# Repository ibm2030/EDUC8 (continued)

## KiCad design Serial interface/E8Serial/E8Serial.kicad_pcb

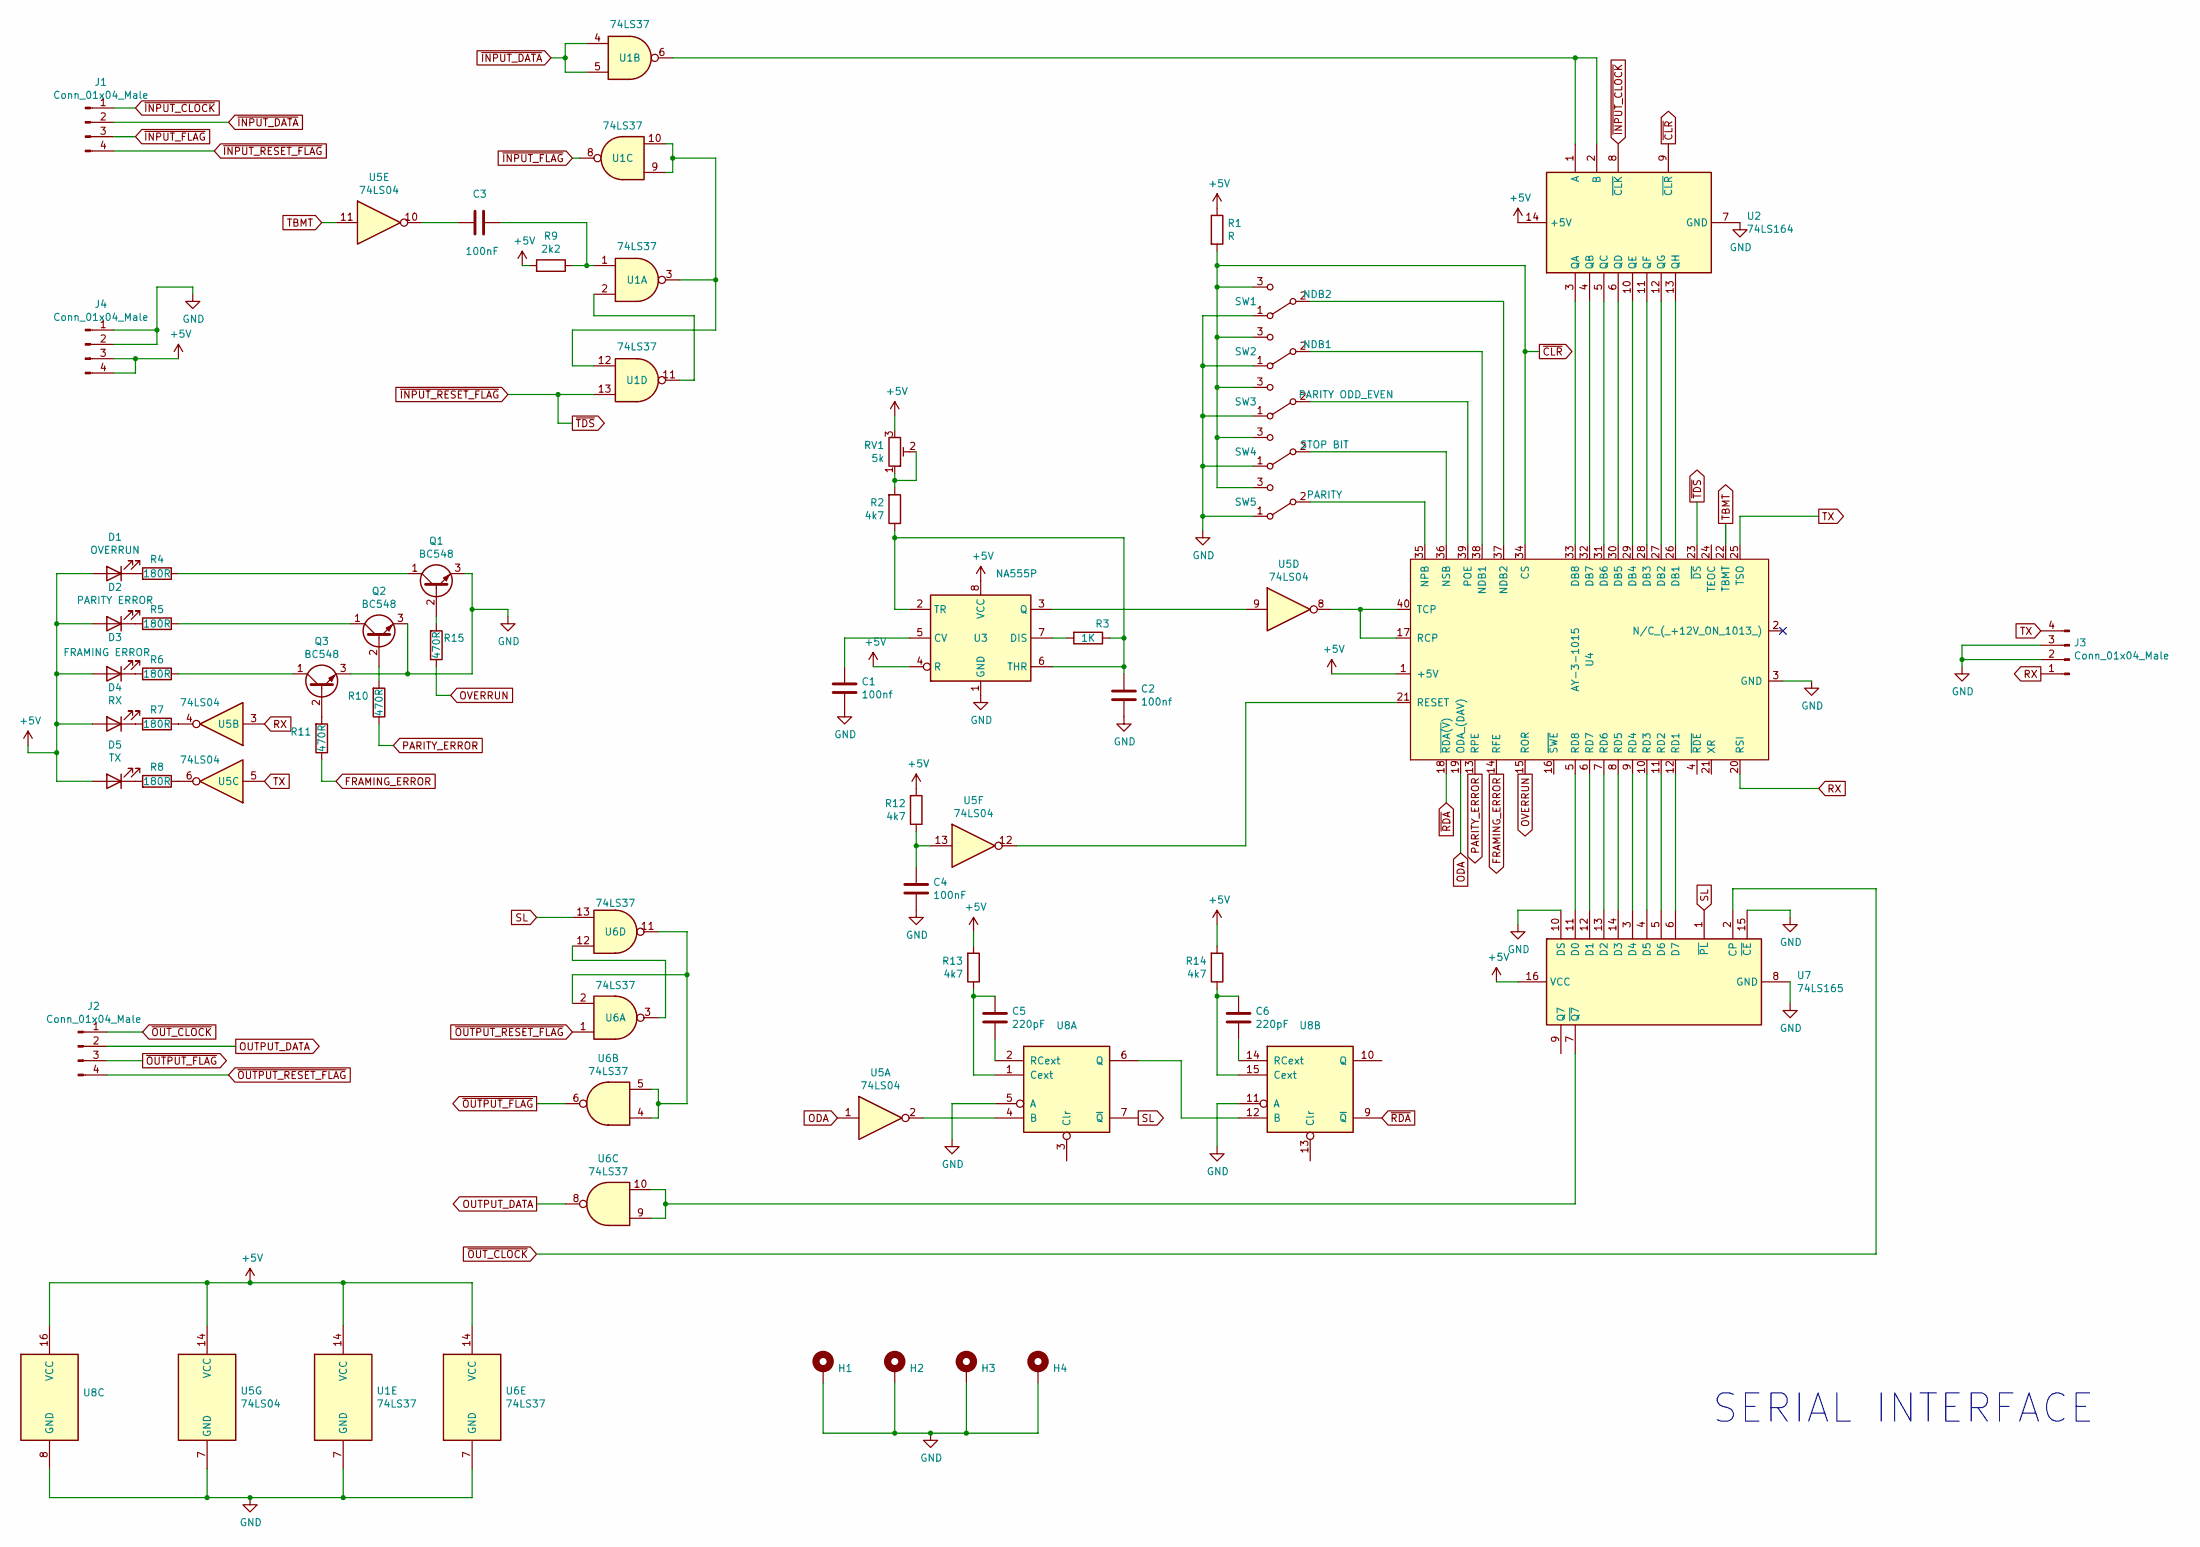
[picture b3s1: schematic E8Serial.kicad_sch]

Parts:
C1, C2: 100nf; C_Disc_D10.0mm_W2.5mm_P5.00mm
C3, C4: 100nF; C_Disc_D10.0mm_W2.5mm_P5.00mm
C5, C6: 220pF; C_Disc_D8.0mm_W2.5mm_P5.00mm
D1: OVERRUN; LED_D5.0mm_Horizontal_O3.81mm_Z9.0mm
D2: PARITY ERROR; LED_D5.0mm_Horizontal_O3.81mm_Z9.0mm
D3: FRAMING ERROR; LED_D5.0mm_Horizontal_O3.81mm_Z9.0mm
D4: RX; LED_D5.0mm_Horizontal_O3.81mm_Z9.0mm
D5: TX; LED_D5.0mm_Horizontal_O3.81mm_Z9.0mm
H1, H2, H3, H4: MountingHole_Pad; MountingHole_3.2mm_M3_Pad_Via
J1, J2, J3, J4: Conn_01x04_Male; PinHeader_1x04_P2.54mm_Vertical
Q1, Q2, Q3: BC548; TO-92_Inline_Wide
R1: R; R_Axial_DIN0207_L6.3mm_D2.5mm_P10.16mm_Horizontal
R2, R12, R13, R14: 4k7; R_Axial_DIN0207_L6.3mm_D2.5mm_P10.16mm_Horizontal
R3: 1K; R_Axial_DIN0207_L6.3mm_D2.5mm_P10.16mm_Horizontal
R4, R5, R6, R7, R8: 180R; R_Axial_DIN0207_L6.3mm_D2.5mm_P10.16mm_Horizontal
R9: 2k2; R_Axial_DIN0207_L6.3mm_D2.5mm_P10.16mm_Horizontal
R10, R11, R15: 470R; R_Axial_DIN0207_L6.3mm_D2.5mm_P10.16mm_Horizontal
RV1: 5k; Potentiometer_Bourns_3006P_Horizontal
SW1: NDB2; S1320_SPDP_Toggle_switch_PCB_right_angle
SW2: NDB1; S1320_SPDP_Toggle_switch_PCB_right_angle
SW3: PARITY ODD_EVEN; S1320_SPDP_Toggle_switch_PCB_right_angle
SW4: STOP BIT; S1320_SPDP_Toggle_switch_PCB_right_angle
SW5: PARITY; S1320_SPDP_Toggle_switch_PCB_right_angle
U1, U6: 74LS37; DIP-14_W7.62mm
U2: 74LS164; DIP-14_W7.62mm
U3: NA555P; DIP-8_W7.62mm
U4: AY-3-1015; DIP-40_W15.24mm
U5: 74LS04; DIP-14_W7.62mm
U7: 74LS165; DIP-16_W7.62mm
U8: DIP-16_W7.62mm_Socket_LongPads

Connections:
+5V: D1.2 (A), D2.2 (A), D3.2 (A), D4.2 (A), D5.2 (A), J4.3, J4.4, R1.1, R9.2, R12.2, R13.2, R14.2, RV1.3, U1.14 (VCC), U2.14 (+5V), U3.4 (R), U3.8 (VCC), U4.1 (+5V), U5.14 (VCC), U6.14 (VCC), U7.16 (VCC), U8.16 (VCC)
FRAMING_ERROR: R11.1, U4.14 (RFE)
GND: C1.2, C2.2, C4.2, H1.1, H2.1, H3.1, H4.1, J3.2, J3.3, J4.1, J4.2, Q1.3 (E), Q2.3 (E), Q3.3 (E), SW1.1 (A), SW2.1 (A), SW3.1 (A), SW4.1 (A), SW5.1 (A), U1.7 (GND), U2.7 (GND), U3.1 (GND), U4.3 (GND), U5.7 (GND), U6.7 (GND), U7.8 (GND), U7.10 (DS), U7.15 (~CE), U8.5 (A), U8.8 (GND), U8.11 (A)
unnamed: C1.1, U3.5 (CV)
unnamed: C2.1, R2.1, R3.1, U3.2 (TR), U3.6 (THR)
unnamed: C3.1, R9.1, U1.1
unnamed: C3.2, U5.10
unnamed: C4.1, R12.1, U5.13
unnamed: C5.1, R13.1, U8.1 (Cext)
unnamed: C5.2, U8.2 (RCext)
unnamed: C6.1, R14.1, U8.15 (Cext)
unnamed: C6.2, U8.14 (RCext)
unnamed: D1.1 (K), R4.2
unnamed: D2.1 (K), R5.2
unnamed: D3.1 (K), R6.2
unnamed: D4.1 (K), R7.2
unnamed: D5.1 (K), R8.2
unnamed: Q1.1 (C), R4.1
unnamed: Q1.2 (B), R15.2
unnamed: Q2.1 (C), R5.1
unnamed: Q2.2 (B), R10.2
unnamed: Q3.1 (C), R6.1
unnamed: Q3.2 (B), R11.2
unnamed: R2.2, RV1.1, RV1.2
unnamed: R3.2, U3.7 (DIS)
unnamed: R7.1, U5.4
unnamed: R8.1, U5.6
unnamed: SW1.2 (B), U4.37 (NDB2)
unnamed: SW2.2 (B), U4.38 (NDB1)
unnamed: SW3.2 (B), U4.39 (POE)
unnamed: SW4.2 (B), U4.36 (NSB)
unnamed: SW5.2 (B), U4.35 (NPB)
unnamed: U1.6, U2.1 (A), U2.2 (B)
unnamed: U1.3, U1.9, U1.10, U1.12
unnamed: U1.2, U1.11
unnamed: U2.3 (QA), U4.33 (DB8)
unnamed: U2.4 (QB), U4.32 (DB7)
unnamed: U2.5 (QC), U4.31 (DB6)
unnamed: U2.6 (QD), U4.30 (DB5)
unnamed: U2.10 (QE), U4.29 (DB4)
unnamed: U2.11 (QF), U4.28 (DB3)
unnamed: U2.12 (QG), U4.27 (DB2)
unnamed: U2.13 (QH), U4.26 (DB1)
unnamed: U3.3 (Q), U5.9
unnamed: U4.5 (RD8), U7.11 (D0)
unnamed: U4.6 (RD7), U7.12 (D1)
unnamed: U4.7 (RD6), U7.13 (D2)
unnamed: U4.8 (RD5), U7.14 (D3)
unnamed: U4.9 (RD4), U7.3 (D4)
unnamed: U4.10 (RD3), U7.4 (D5)
unnamed: U4.11 (RD2), U7.5 (D6)
unnamed: U4.12 (RD1), U7.6 (D7)
unnamed: U4.17 (RCP), U4.40 (TCP), U5.8
unnamed: U4.21 (RESET), U5.12
unnamed: U5.2, U8.4 (B)
unnamed: U6.9, U6.10, U7.7 (~Q7)
unnamed: U6.2, U6.4, U6.5, U6.11
unnamed: U6.3, U6.12
unnamed: U8.6 (Q), U8.12 (B)
ODA: U4.19 (ODA_(DAV)), U5.1
OUTPUT_DATA: J2.2, U6.8
OVERRUN: R15.1, U4.15 (ROR)
PARITY_ERROR: R10.1, U4.13 (RPE)
RX: J3.1, U4.20 (RSI), U5.3
SL: U6.13, U7.1 (~PL), U8.7 (~Q)
TBMT: U4.22 (TBMT), U5.11
TX: J3.4, U4.25 (TSO), U5.5
~CLR: R1.2, SW1.3 (C), SW2.3 (C), SW3.3 (C), SW4.3 (C), SW5.3 (C), U2.9 (~CLR), U4.34 (CS)
~INPUT_CLOCK: J1.1, U2.8 (~CLK)
~INPUT_DATA: J1.2, U1.4, U1.5
~INPUT_FLAG: J1.3, U1.8
~INPUT_RESET_FLAG: J1.4, U1.13, U4.23 (~DS)
~OUTPUT_FLAG: J2.3, U6.6
~OUTPUT_RESET_FLAG: J2.4, U6.1
~OUT_CLOCK: J2.1, U7.2 (CP)
~RDA: U4.18 (~RDA(V)), U8.9 (~Q)

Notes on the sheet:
SERIAL INTERFACE

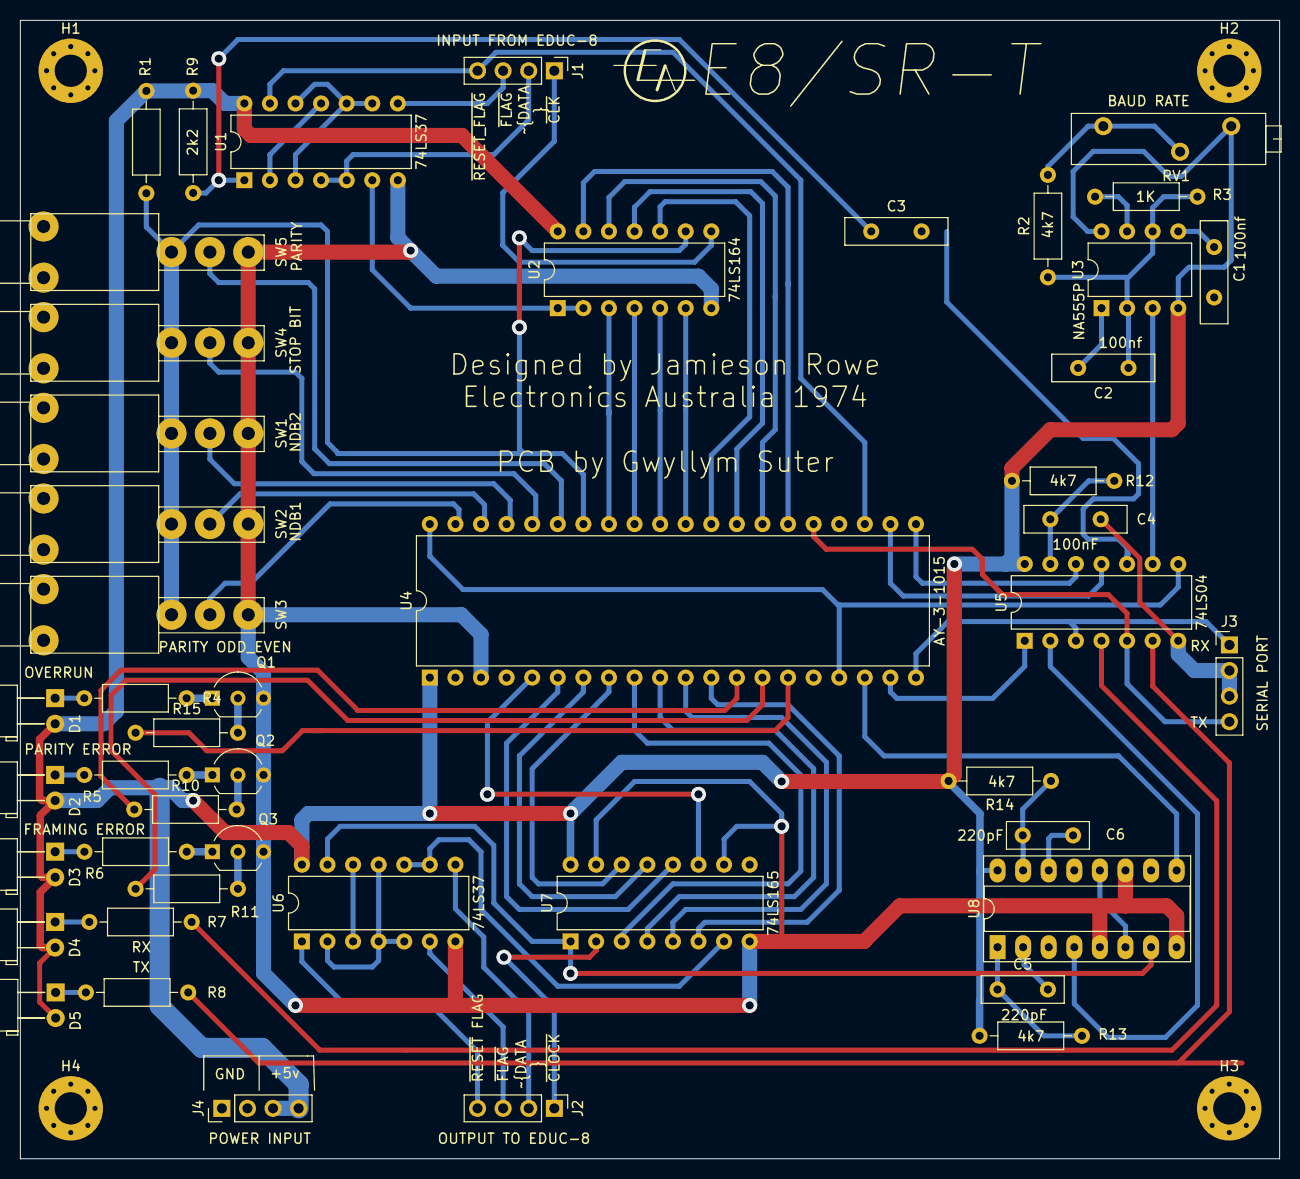
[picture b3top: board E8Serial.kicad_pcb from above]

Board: 2 copper layers, 125.0 x 113.0 mm, 51 parts (0 on the bottom side), 76 nets.

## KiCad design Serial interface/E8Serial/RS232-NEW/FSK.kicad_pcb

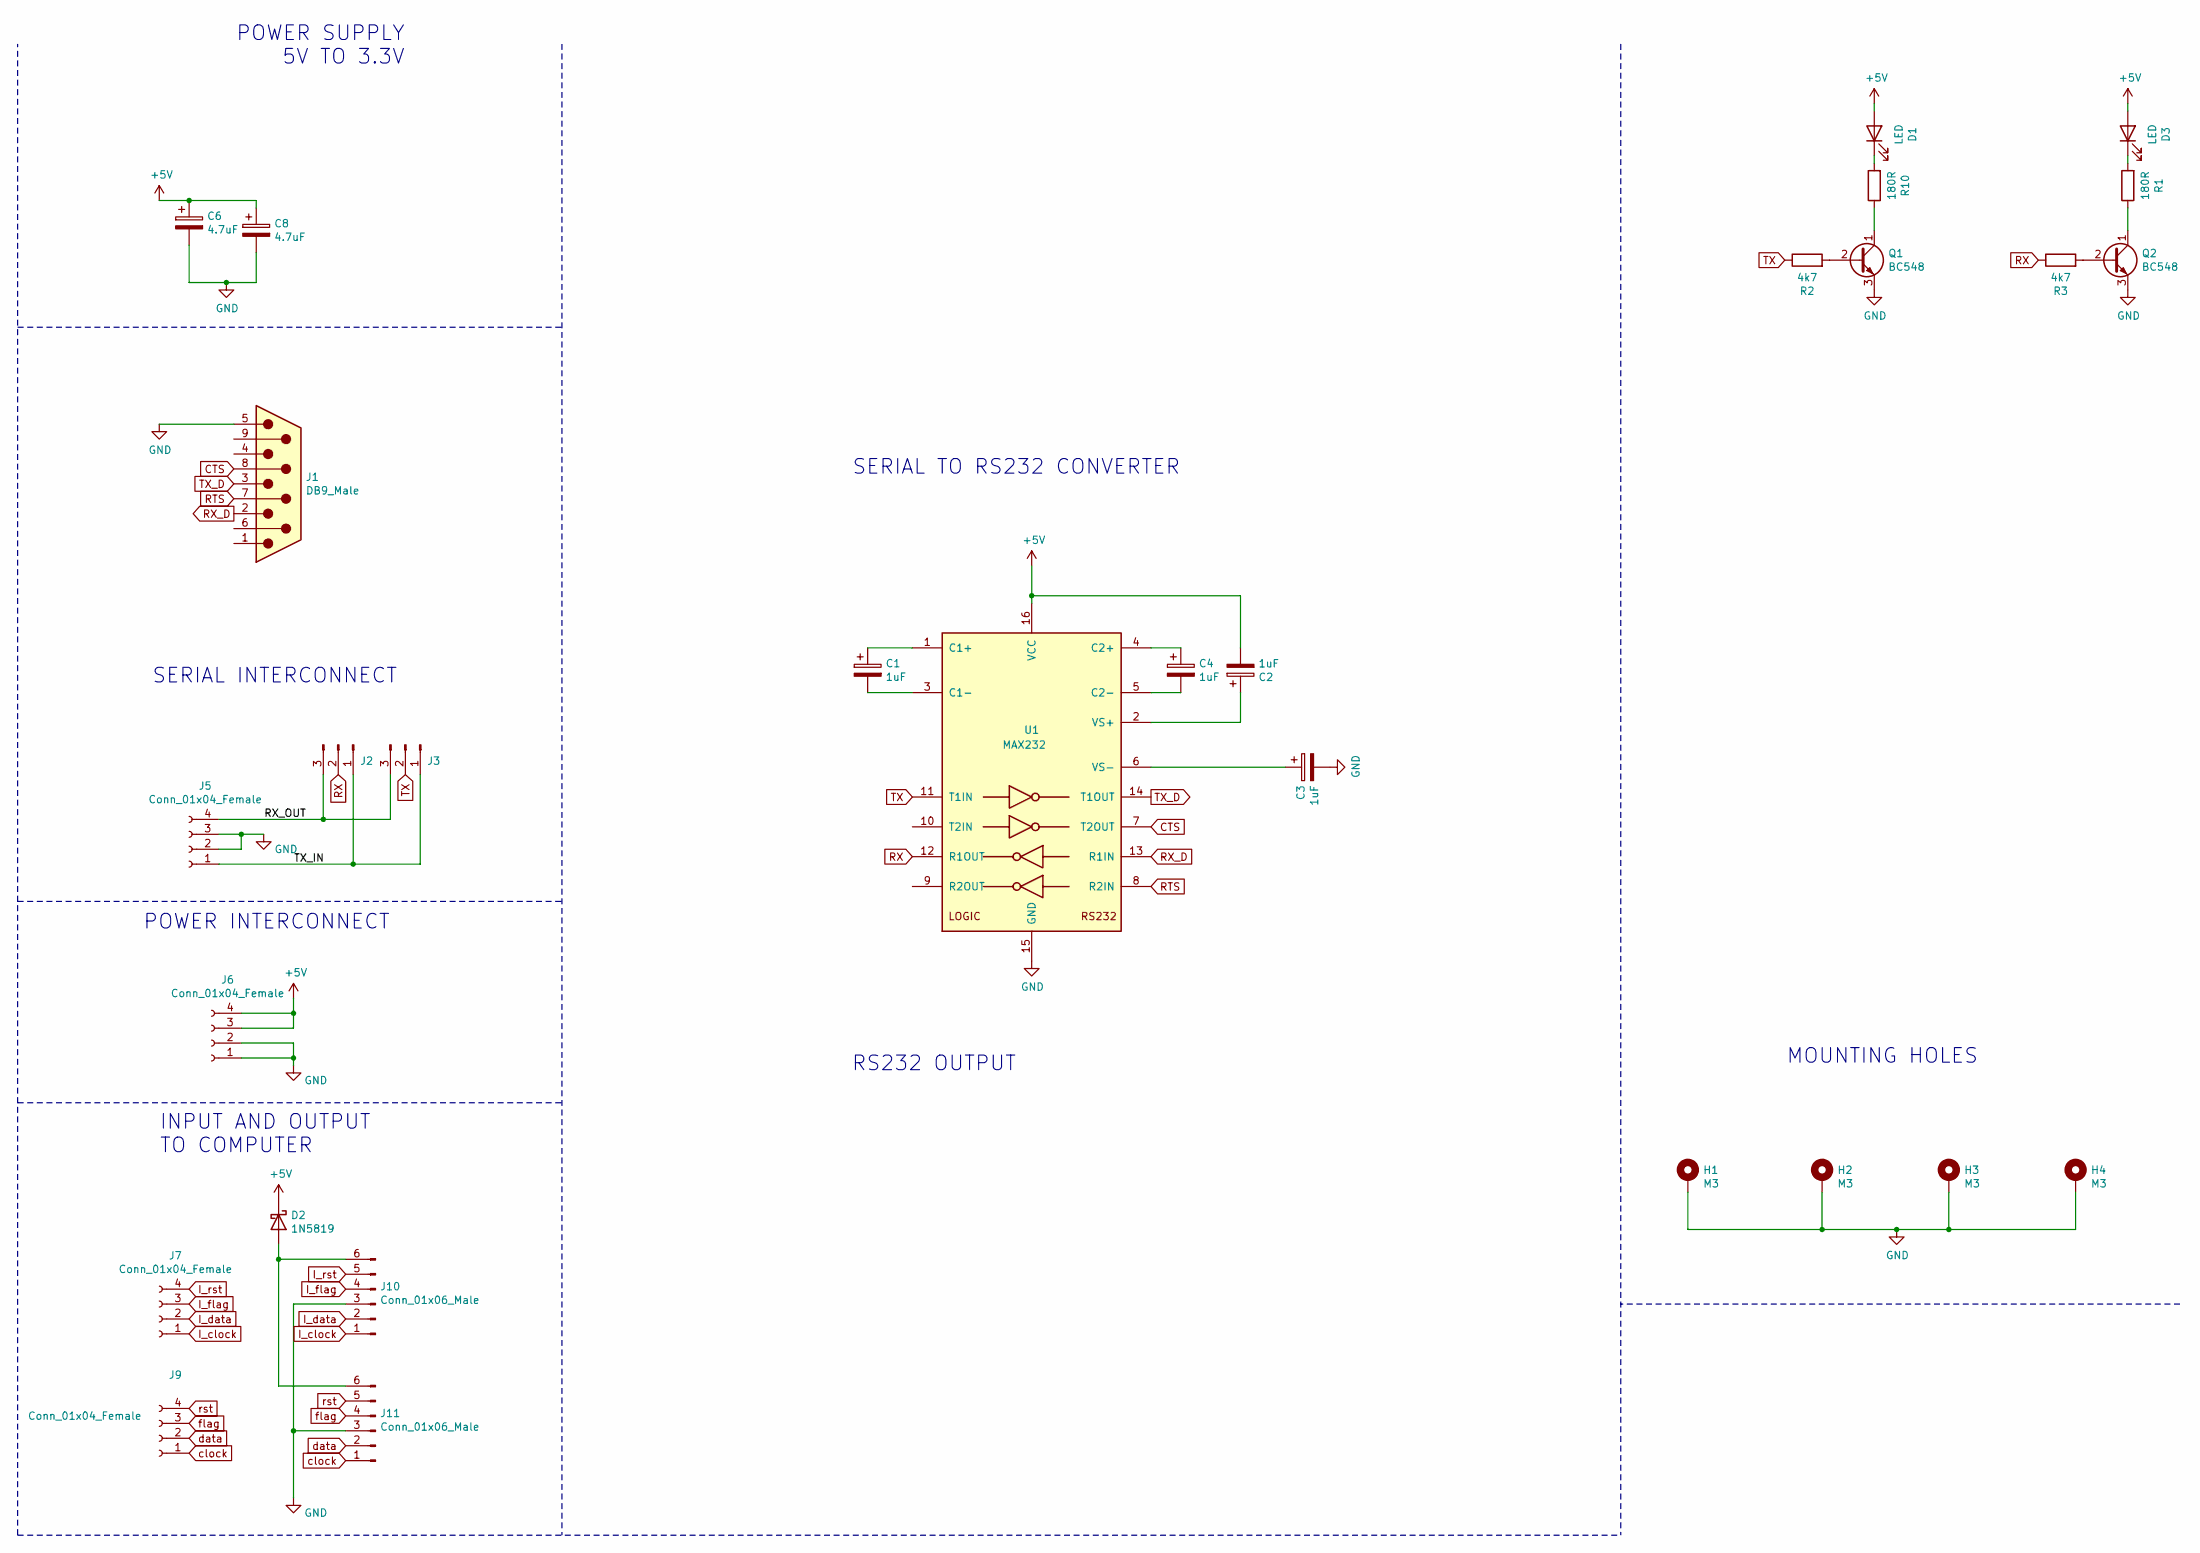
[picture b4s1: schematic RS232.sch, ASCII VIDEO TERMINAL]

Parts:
C1, C2, C3, C4: 1uF; CP_Radial_D5.0mm_P2.50mm
C6, C8: 4.7uF; CP_Axial_L11.0mm_D6.0mm_P18.00mm_Horizontal
D1, D3: LED; LED_D5.0mm_Horizontal_O1.27mm_Z3.0mm
D2: 1N5819; D_DO-41_SOD81_P10.16mm_Horizontal
H1, H2, H3, H4: M3; MountingHole_3.2mm_M3_Pad_Via
J1: DB9_Male; DSUB-9_Male_Horizontal_P2.77x2.84mm_EdgePinOffset4.94mm_Hou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
J2, J3: Conn_01x03_Male; PinHeader_1x03_P2.54mm_Vertical
J5, J6, J7, J9: Conn_01x04_Female; PinSocket_1x04_P2.54mm_Vertical
J10, J11: Conn_01x06_Male; Molex_KK-254_AE-6410-06A_1x06_P2.54mm_Vertical
Q1, Q2: BC548; TO-92_Inline_Wide
R1, R10: 180R; R_Axial_DIN0207_L6.3mm_D2.5mm_P10.16mm_Horizontal
R2, R3: 4k7; R_Axial_DIN0207_L6.3mm_D2.5mm_P10.16mm_Horizontal
U1: MAX232; DIP-16_W7.62mm

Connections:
+5V: C2.2, C6.1, C8.1, D1.2 (A), D2.1 (K), D3.2 (A), J6.3, J6.4, U1.16 (VCC)
/RX_OUT: J2.3, J3.3, J5.4
/TX_IN: J2.1, J3.1, J5.1
CTS: J1.8, U1.7 (T2OUT)
GND: C3.2, C6.2, C8.2, H1.1, H2.1, H3.1, H4.1, J1.5, J5.2, J5.3, J6.1, J6.2, J10.3, J11.3, Q1.3 (E), Q2.3 (E), U1.15 (GND)
I_clock: J7.1, J10.1
I_data: J7.2, J10.2
I_flag: J7.3, J10.4
I_rst: J7.4, J10.5
unnamed: C1.1, U1.1 (C1+)
unnamed: C1.2, U1.3 (C1-)
unnamed: C2.1, U1.2 (VS+)
unnamed: C3.1, U1.6 (VS-)
unnamed: C4.1, U1.4 (C2+)
unnamed: C4.2, U1.5 (C2-)
unnamed: D1.1 (K), R10.2
unnamed: D2.2 (A), J10.6, J11.6
unnamed: D3.1 (K), R1.2
unnamed: Q1.1 (C), R10.1
unnamed: Q1.2 (B), R2.2
unnamed: Q2.1 (C), R1.1
unnamed: Q2.2 (B), R3.2
RTS: J1.7, U1.8 (R2IN)
RX: J2.2, R3.1, U1.12 (R1OUT)
RX_D: J1.2, U1.13 (R1IN)
TX: J3.2, R2.1, U1.11 (T1IN)
TX_D: J1.3, U1.14 (T1OUT)
clock: J9.1, J11.1
data: J9.2, J11.2
flag: J9.3, J11.4
rst: J9.4, J11.5

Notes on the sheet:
SERIAL INTERCONNECT
POWER INTERCONNECT
INPUT AND OUTPUT TO COMPUTER
SERIAL TO RS232 CONVERTER
RS232 OUTPUT
POWER SUPPLY 5V TO 3.3V
MOUNTING HOLES

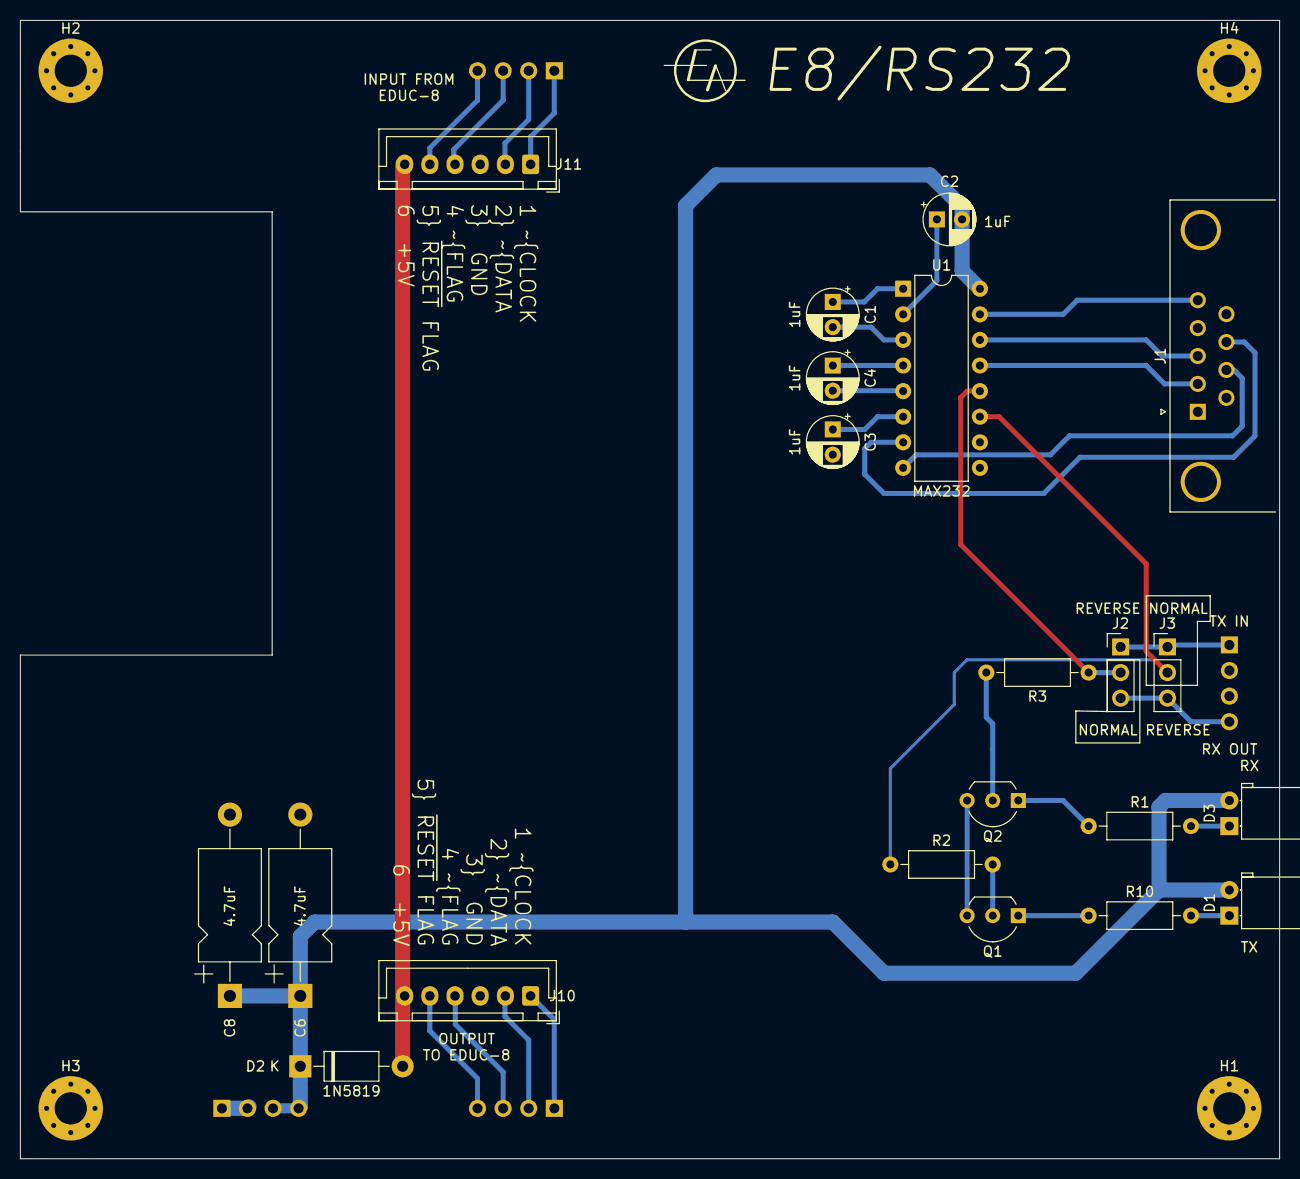
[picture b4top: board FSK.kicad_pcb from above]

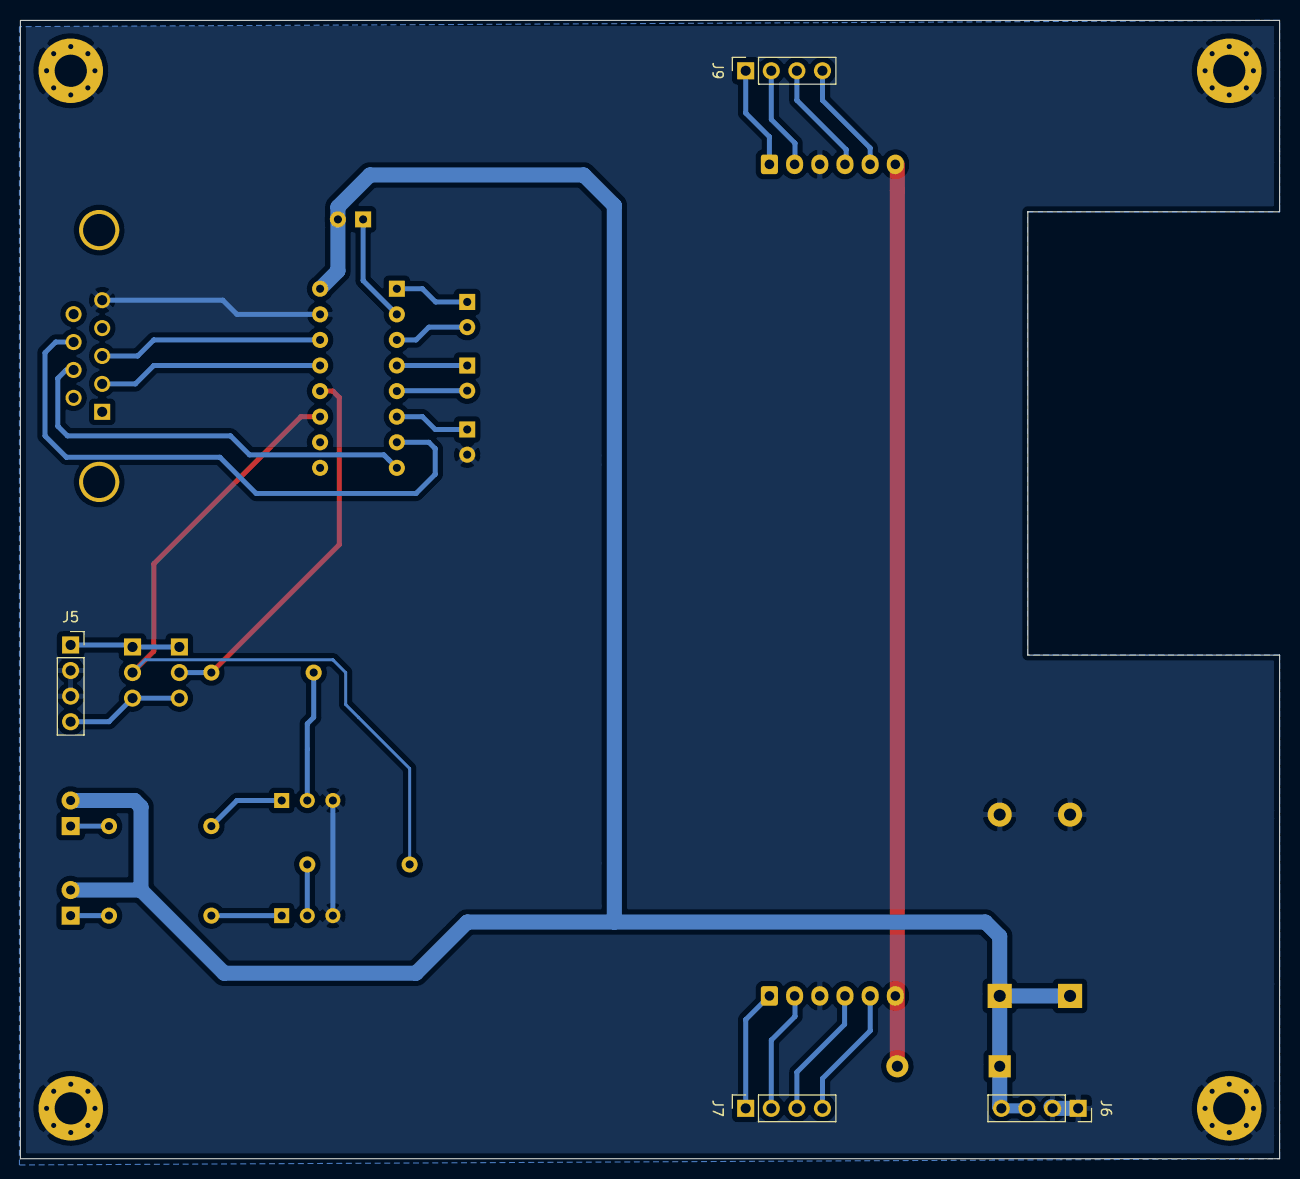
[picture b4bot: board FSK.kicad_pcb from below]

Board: 2 copper layers, 125.0 x 113.0 mm, 29 parts (4 on the bottom side), 31 nets.

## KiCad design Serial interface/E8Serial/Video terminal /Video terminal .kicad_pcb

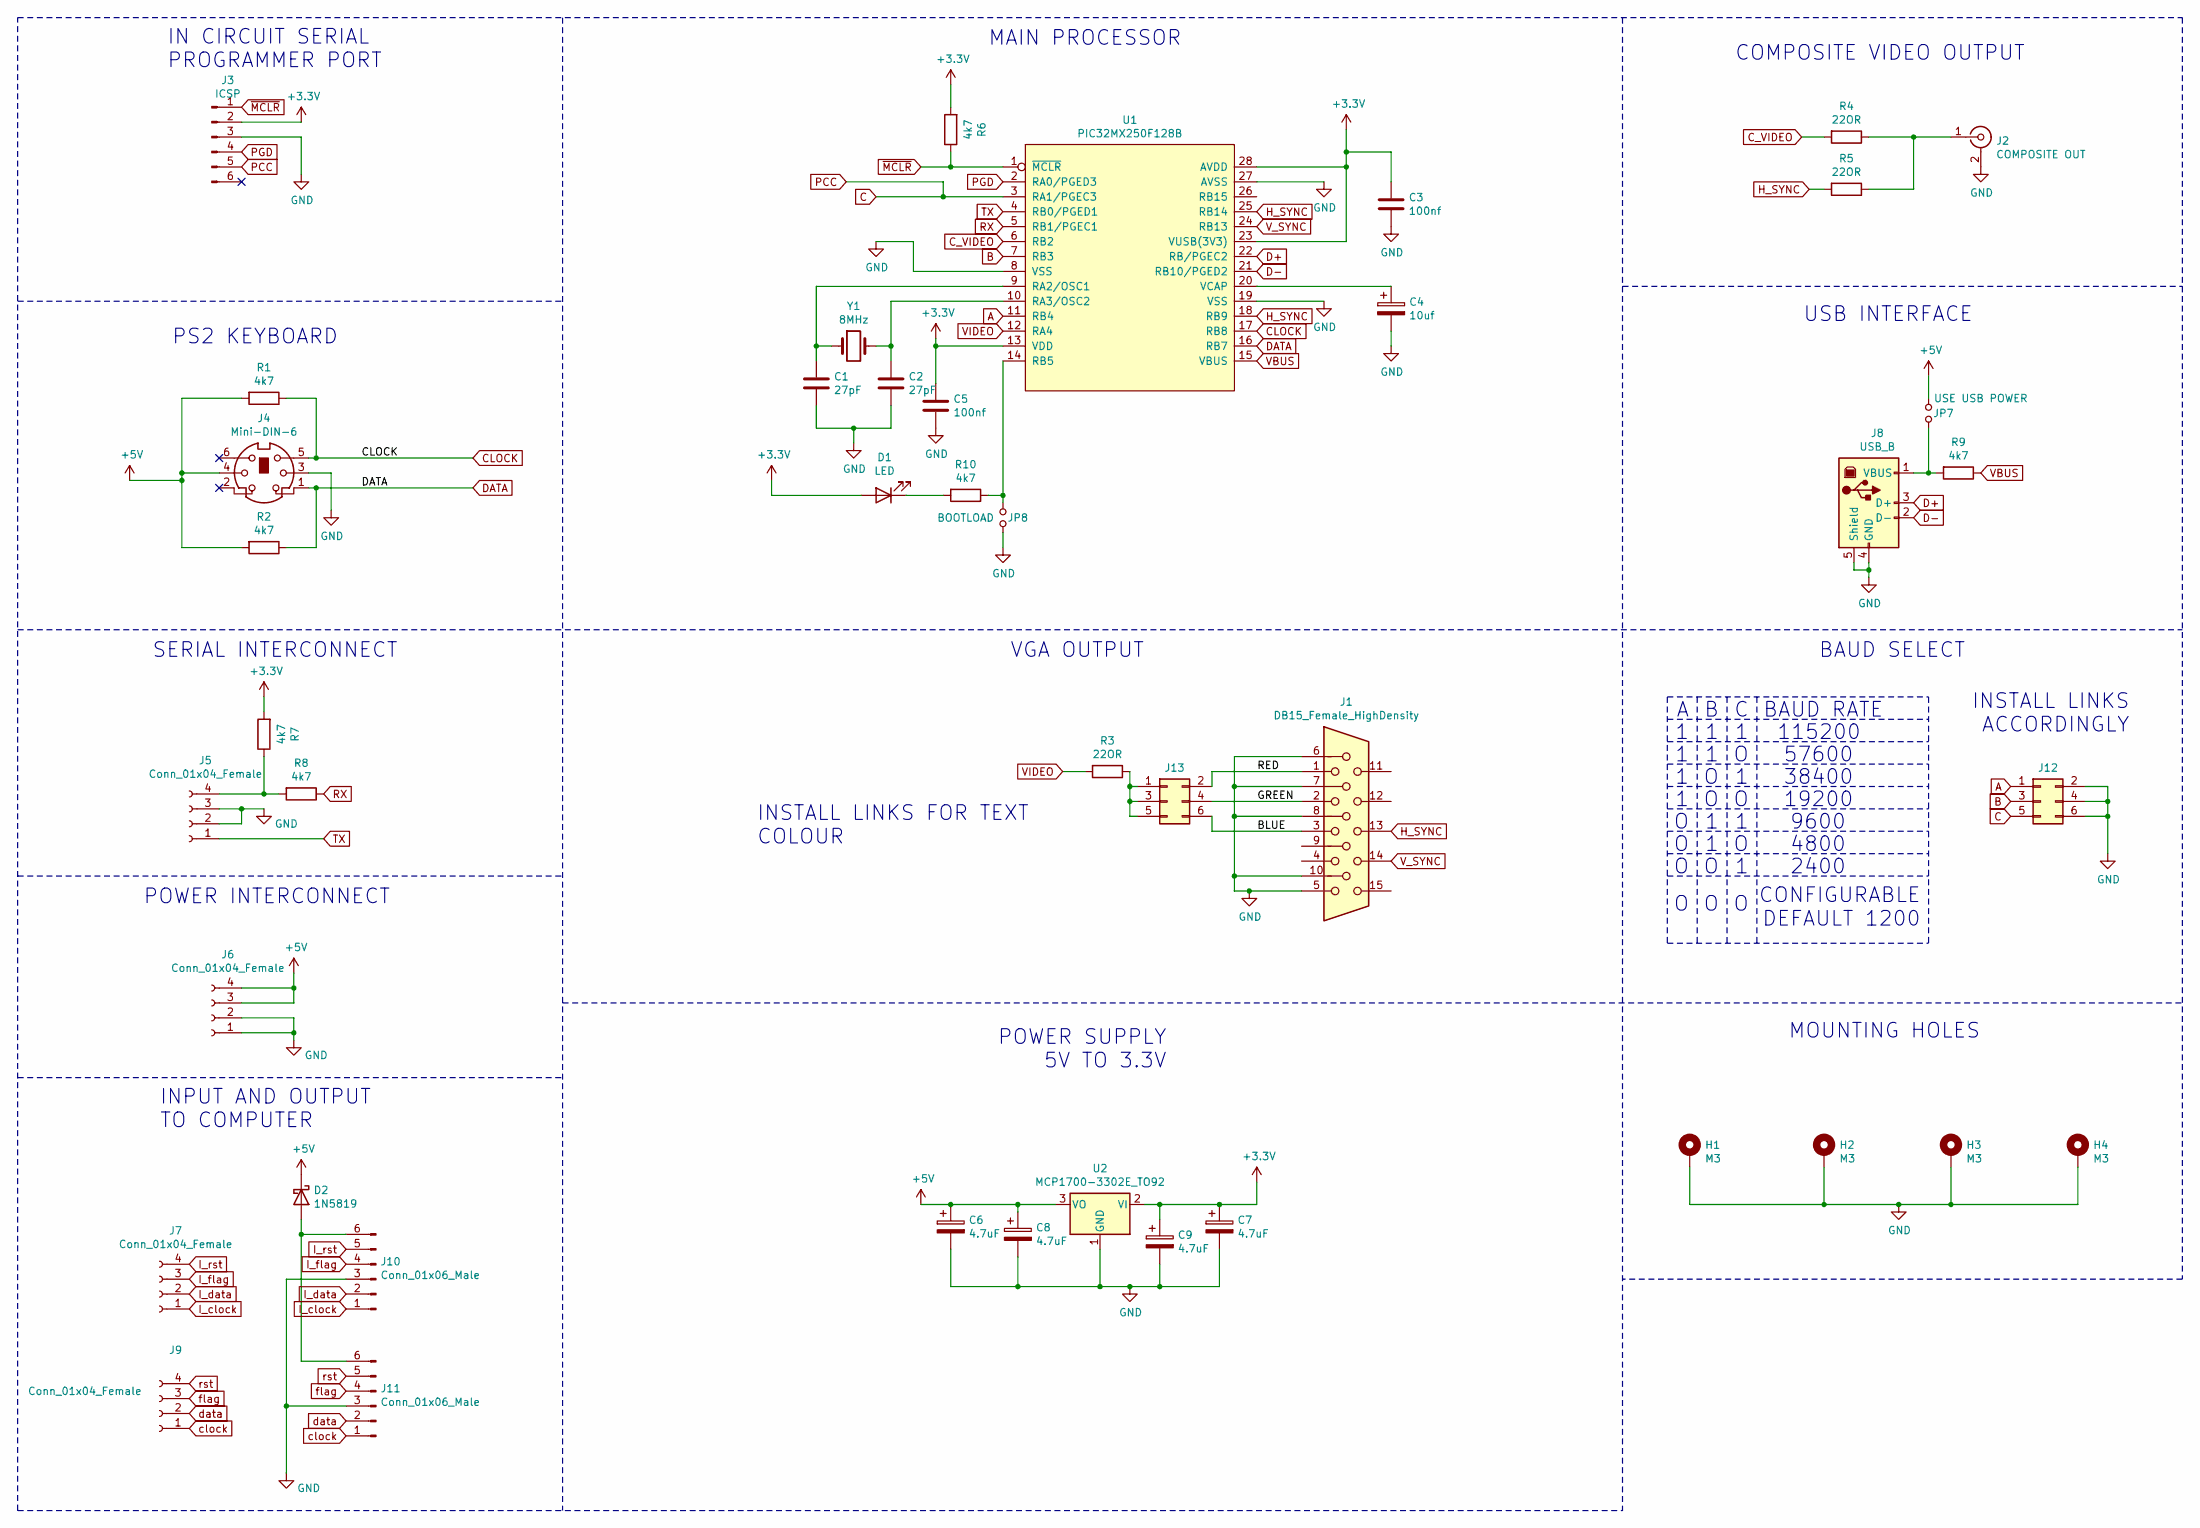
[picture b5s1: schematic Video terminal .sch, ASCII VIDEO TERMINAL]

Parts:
C1, C2: 27pF; C_Disc_D4.3mm_W1.9mm_P5.00mm
C3, C5: 100nf; C_Rect_L7.0mm_W3.5mm_P5.00mm
C4: 10uf; CP_Radial_D5.0mm_P2.50mm
C6, C7, C8, C9: 4.7uF; CP_Axial_L11.0mm_D6.0mm_P18.00mm_Horizontal
D1: LED; LED_D5.0mm_Horizontal_O1.27mm_Z3.0mm
D2: 1N5819; D_DO-41_SOD81_P10.16mm_Horizontal
H1, H2, H3, H4: M3; MountingHole_3.2mm_M3_Pad_Via
J1: DB15_Female_HighDensity; DSUB-15-HD_Female_Horizontal_P2.29x1.98mm_EdgePinOffset8.35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
J2: COMPOSITE OUT; BNC_Amphenol_031-6575_Horizontal
J3: ICSP; PinHeader_1x06_P2.54mm_Vertical
J4: Mini-DIN-6; 6_pin_mini_din
J5, J6, J7, J9: Conn_01x04_Female; PinSocket_1x04_P2.54mm_Vertical
J8: USB_B; USB_B_Lumberg_2411_02_Horizontal
J10, J11: Conn_01x06_Male; Molex_KK-254_AE-6410-06A_1x06_P2.54mm_Vertical
J12, J13: Conn_02x03_Odd_Even; PinHeader_2x03_P2.54mm_Vertical
JP7: USE USB POWER; PinHeader_2x01_P2.54mm_Vertical
JP8: BOOTLOAD; PinHeader_2x01_P2.54mm_Vertical
R1, R2, R6, R7, R8, R9, R10: 4k7; R_Axial_DIN0207_L6.3mm_D2.5mm_P10.16mm_Horizontal
R3, R4, R5: 22OR; R_Axial_DIN0207_L6.3mm_D2.5mm_P10.16mm_Horizontal
U1: PIC32MX250F128B; DIP-28_W7.62mm
U2: MCP1700-3302E_TO92; TO-92_Inline_Wide
Y1: 8MHz; Crystal_HC49-4H_Vertical

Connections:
+3V3: C3.1, C5.1, C7.1, C9.1, D1.2 (A), J3.2, R6.2, R7.2, U1.13 (VDD), U1.23 (VUSB(3V3)), U1.28 (AVDD), U2.2 (VI)
+5V: C6.1, C8.1, D2.1 (K), J4.4, J6.3, J6.4, JP7.1, R1.2, R2.2, U2.3 (VO)
/BLUE: J1.3, J13.6
/GREEN: J1.2, J13.4
/RED: J1.1, J13.2
A: J12.1, U1.11 (RB4)
B: J12.3, U1.7 (RB3)
C: J3.5, J12.5, U1.3 (RA1/PGEC3)
CLOCK: J4.5, R1.1, U1.17 (RB8)
C_VIDEO: R4.2, U1.6 (RB2)
D+: J8.3 (D+), U1.22 (RB/PGEC2)
D-: J8.2 (D-), U1.21 (RB10/PGED2)
DATA: J4.1, R2.1, U1.16 (RB7)
GND: C1.2, C2.2, C3.2, C4.2, C5.2, C6.2, C7.2, C8.2, C9.2, H1.1, H2.1, H3.1, H4.1, J1.5, J1.6, J1.7, J1.8, J1.10, J2.2 (Ext), J3.3, J4.3, J5.2, J5.3, J6.1, J6.2, J8.4 (GND), J8.5 (Shield), J10.3, J11.3, J12.2, J12.4, J12.6, JP8.2, U1.8 (VSS), U1.19 (VSS), U1.27 (AVSS), U2.1 (GND)
H_SYNC: J1.13, R5.2, U1.18 (RB9), U1.25 (RB14)
I_clock: J7.1, J10.1
I_data: J7.2, J10.2
I_flag: J7.3, J10.4
I_rst: J7.4, J10.5
unnamed: C1.1, U1.9 (RA2/OSC1), Y1.1
unnamed: C2.1, U1.10 (RA3/OSC2), Y1.2
unnamed: C4.1, U1.20 (VCAP)
unnamed: D1.1 (K), R10.2
unnamed: D2.2 (A), J10.6, J11.6
unnamed: J2.1 (In), R4.1, R5.1
unnamed: J5.4, R7.1, R8.2
unnamed: J8.1 (VBUS), JP7.2, R9.2
unnamed: J13.1, J13.3, J13.5, R3.1
unnamed: JP8.1, R10.1, U1.14 (RB5)
PGD: J3.4, U1.2 (RA0/PGED3)
RX: R8.1, U1.5 (RB1/PGEC1)
TX: J5.1, U1.4 (RB0/PGED1)
VBUS: R9.1, U1.15 (VBUS)
VIDEO: R3.2, U1.12 (RA4)
V_SYNC: J1.14, U1.24 (RB13)
clock: J9.1, J11.1
data: J9.2, J11.2
flag: J9.3, J11.4
rst: J9.4, J11.5
~MCLR: J3.1, R6.1, U1.1 (~MCLR)

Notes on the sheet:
PS2 KEYBOARD
IN CIRCUIT SERIAL PROGRAMMER PORT
SERIAL INTERCONNECT
POWER INTERCONNECT
INPUT AND OUTPUT TO COMPUTER
MAIN PROCESSOR
VGA OUTPUT
INSTALL LINKS FOR TEXT COLOUR
POWER SUPPLY 5V TO 3.3V
BAUD SELECT
BAUD RATE
115200
57600
38400
19200
9600
4800
2400
CONFIGURABLE DEFAULT 1200
INSTALL LINKS ACCORDINGLY
MOUNTING HOLES
USB INTERFACE
COMPOSITE VIDEO OUTPUT
